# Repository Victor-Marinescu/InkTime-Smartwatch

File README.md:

# InkTime Smartwatch Project

**InkTime** este un smartwatch conceptual bazat pe microcontrolerul **nRF52840**, proiectat pentru autonomie ridicată prin utilizarea unui ecran E-Paper și optimizarea consumului de energie.

---

## 1. Diagramă Bloc
Sistemul este organizat în jurul MCU-ului nRF52840, care gestionează comunicația cu senzorii via I2C și controlul ecranului via SPI.

## 2. Bill Of Materials (BOM)

| Componentă | Descriere | Datasheet |
| :--- | :--- | :--- |
| **nRF52840** | MCU Bluetooth 5.4, ARM Cortex-M4 | [Link](https://jlcpcb.com/partdetail/NordicSemicon-NRF52840_QFAA_FR7/C3606653) |
| **5034802400** | 1.54" E-Paper Display (SPI) | [Link](https://jlcpcb.com/partdetail/MOLEX-5034802400/C122434) |
| **MAX17048** | Fuel Gauge (Monitorizare Baterie) | [Link](https://jlcpcb.com/partdetail/2777647-MAX17048GT10/C2682616) |
| **DRV2605** | Haptic Driver (LRA/ERM) | [Link](https://jlcpcb.com/partdetail/TexasInstruments-DRV2605YZFR/C81079) |
| **LSM6DS3** | IMU (Accelerometru & Giroscop) | [Link](https://jlcpcb.com/partdetail/STMicroelectronics-LSM6DS3TR/C95230) |
| **BQ25180** | IC Management Încărcare Baterie | [Link](https://jlcpcb.com/partdetail/TexasInstruments-BQ25180YBGR/C3682423) |
| **RT6160** | Regulator Buck-Boost 3.3V 2.4A | [Link](https://jlcpcb.com/partdetail/RichtekTech-RT6160AWSC/C7065276) |

---

## 3. Descriere Funcționalitate Hardware

### Module și Senzori
* **Microcontroler (MCU):** nRF52840 (AQFN-73) coordonează procesele BLE și perifericele. Decuplare locală via C14 (4.7 µF), C7/C8/C12 (100 nF).
* **Afișaj E-Paper:** Conectat prin **SPI**. Include pompă de tensiune cu L5 (68 µH) și switch de alimentare Q1/Q3 pentru consum zero în sleep.
* **Haptic Feedback:** Driver DRV2605 (I2C: 0x5A) capabil să ruleze peste 123 de efecte tactile din librăria ROM.
* **Power Management:** * **BQ25180:** Încărcător inteligent (I2C: 0x6A) cu Power Path.
    * **MAX17048:** Monitorizare SOC (I2C: 0x36) via algoritm ModelGauge.
    * **RT6160:** Buck-Boost pentru prag stabil de 3.3V chiar și la descărcarea bateriei sub 3.3V.

---

## 4. Configurație Detaliată Pini (nRF52840)

Am extras configurația completă a pinilor conform mapării hardware finale:

| Pin MCU | AQFN-73 | Funcție | Destinație Hardware | Note Tehnice |
| :--- | :--- | :--- | :--- | :--- |
| **P0.02** | A12 | **SCK** | J1 pin 14 (EPD) | Clock SPI Afișaj |
| **P0.03** | B13 | **MOSI** | J1 pin 15 (EPD) | Date SPI Afișaj |
| **P0.05** | A14 | **CS** | J1 pin 13 (EPD) | Chip Select (Activ LOW) |
| **P0.06** | B15 | **SDA** | I2C Bus Shared | Date senzori (R18 pull-up 3.3k) |
| **P0.07** | A16 | **SCL** | I2C Bus Shared | Clock senzori (R17 pull-up 3.3k) |
| **P0.15** | B19 | **EPD_DC** | J1 pin 11 (EPD) | Data/Command Select |
| **P0.16** | A20 | **EPD_RST**| J1 pin 10 (EPD) | Reset Hardware Afișaj |
| **P0.17** | B21 | **BUSY** | J1 pin 9 (EPD) | Monitorizare stare afișaj |
| **P1.01** | AD22 | **EPD_EN** | Q1 PMOS Gate | Control Power-Cut ecran |
| **P0.13** | AD16 | **SW_UP** | Buton UP | Intrare Digitală (R14 pull-up 10k) |
| **P0.12** | AC17 | **SW_ENT**| Buton ENTER | Intrare Digitală (R15 pull-up 10k) |
| **P0.11** | AD18 | **SW_DN** | Buton DOWN | Intrare Digitală (R16 pull-up 10k) |
| **ANT** | H23 | **RF** | Antenă Ceratent | Adaptare 50 Ω (L1, C3, C4) |
| **SWDIO** | AC24 | **DIO** | J2 pin 2 (Debug) | Programare Serial Wire Data |
| **SWDCLK**| AA24 | **CLK** | J2 pin 4 (Debug) | Programare Serial Wire Clock |

---

## 5. Strategie Design și Review

### Detalii PCB (4 Layere)
* **Lățime Trasee Putere:** 0.3 mm pentru rețelele `VBUS`, `VBAT`, `VREG` și `3V3`.
* **Trasee Date:** 0.15 mm pentru I2C, SPI și semnalele de control.
* **Stackup:**
    * **Layer 1 (Top):** Componente, RF (Antenă) și semnale critice.
    * **Layer 2:** Plan dedicat de alimentare (3.3V / VREG).
    * **Layer 63 (Mid):** Trasee secundare de date.
    * **Layer 64 (Bottom):** Plan de masă (GND) continuu sub zona RF.

### Estimare Consum Energetic
* **MCU (Sleep + RTC + BLE Adv 1Hz):** ~200 µA
* **BMA423 (Pedometru Low-Power):** ~130 µA
* **MAX17048 (Activ):** ~23 µA
* **RT6160 Quiescent:** ~30 µA
* **Total Mediu:** **~390 µA**
* **Autonomie:** ~10 zile (baterie 100mAh) / ~25 zile (baterie 250mAh).

---

## 6. Erori DRC Ignorate 

### Overlap (6 erori)
* **Localizare:** Cele 3 butoane laterale (UP, ENT, DN).
* **Justificare:** Suprapunere asumată între pinii mecanici și via-urile de semnal.

### Drill size (11 erori)
* **Localizare:** Pinii înconjurați de alți pini, fara acces la exterior.
* **Justificare:** S-a folosit câte un via pentru a face conexiunea între pini fără a avea erori de tip Copper Clearance.

### Board Outline Clearance (4 erori)
* **Localizare:** Conector USB-C (J4).
* **Justificare:** Cupru extins până în Dimension layer pentru a asigura fixarea structurală a mufei la marginea carcasei.

---
Licensed under the [Apache 2.0](LICENSE).

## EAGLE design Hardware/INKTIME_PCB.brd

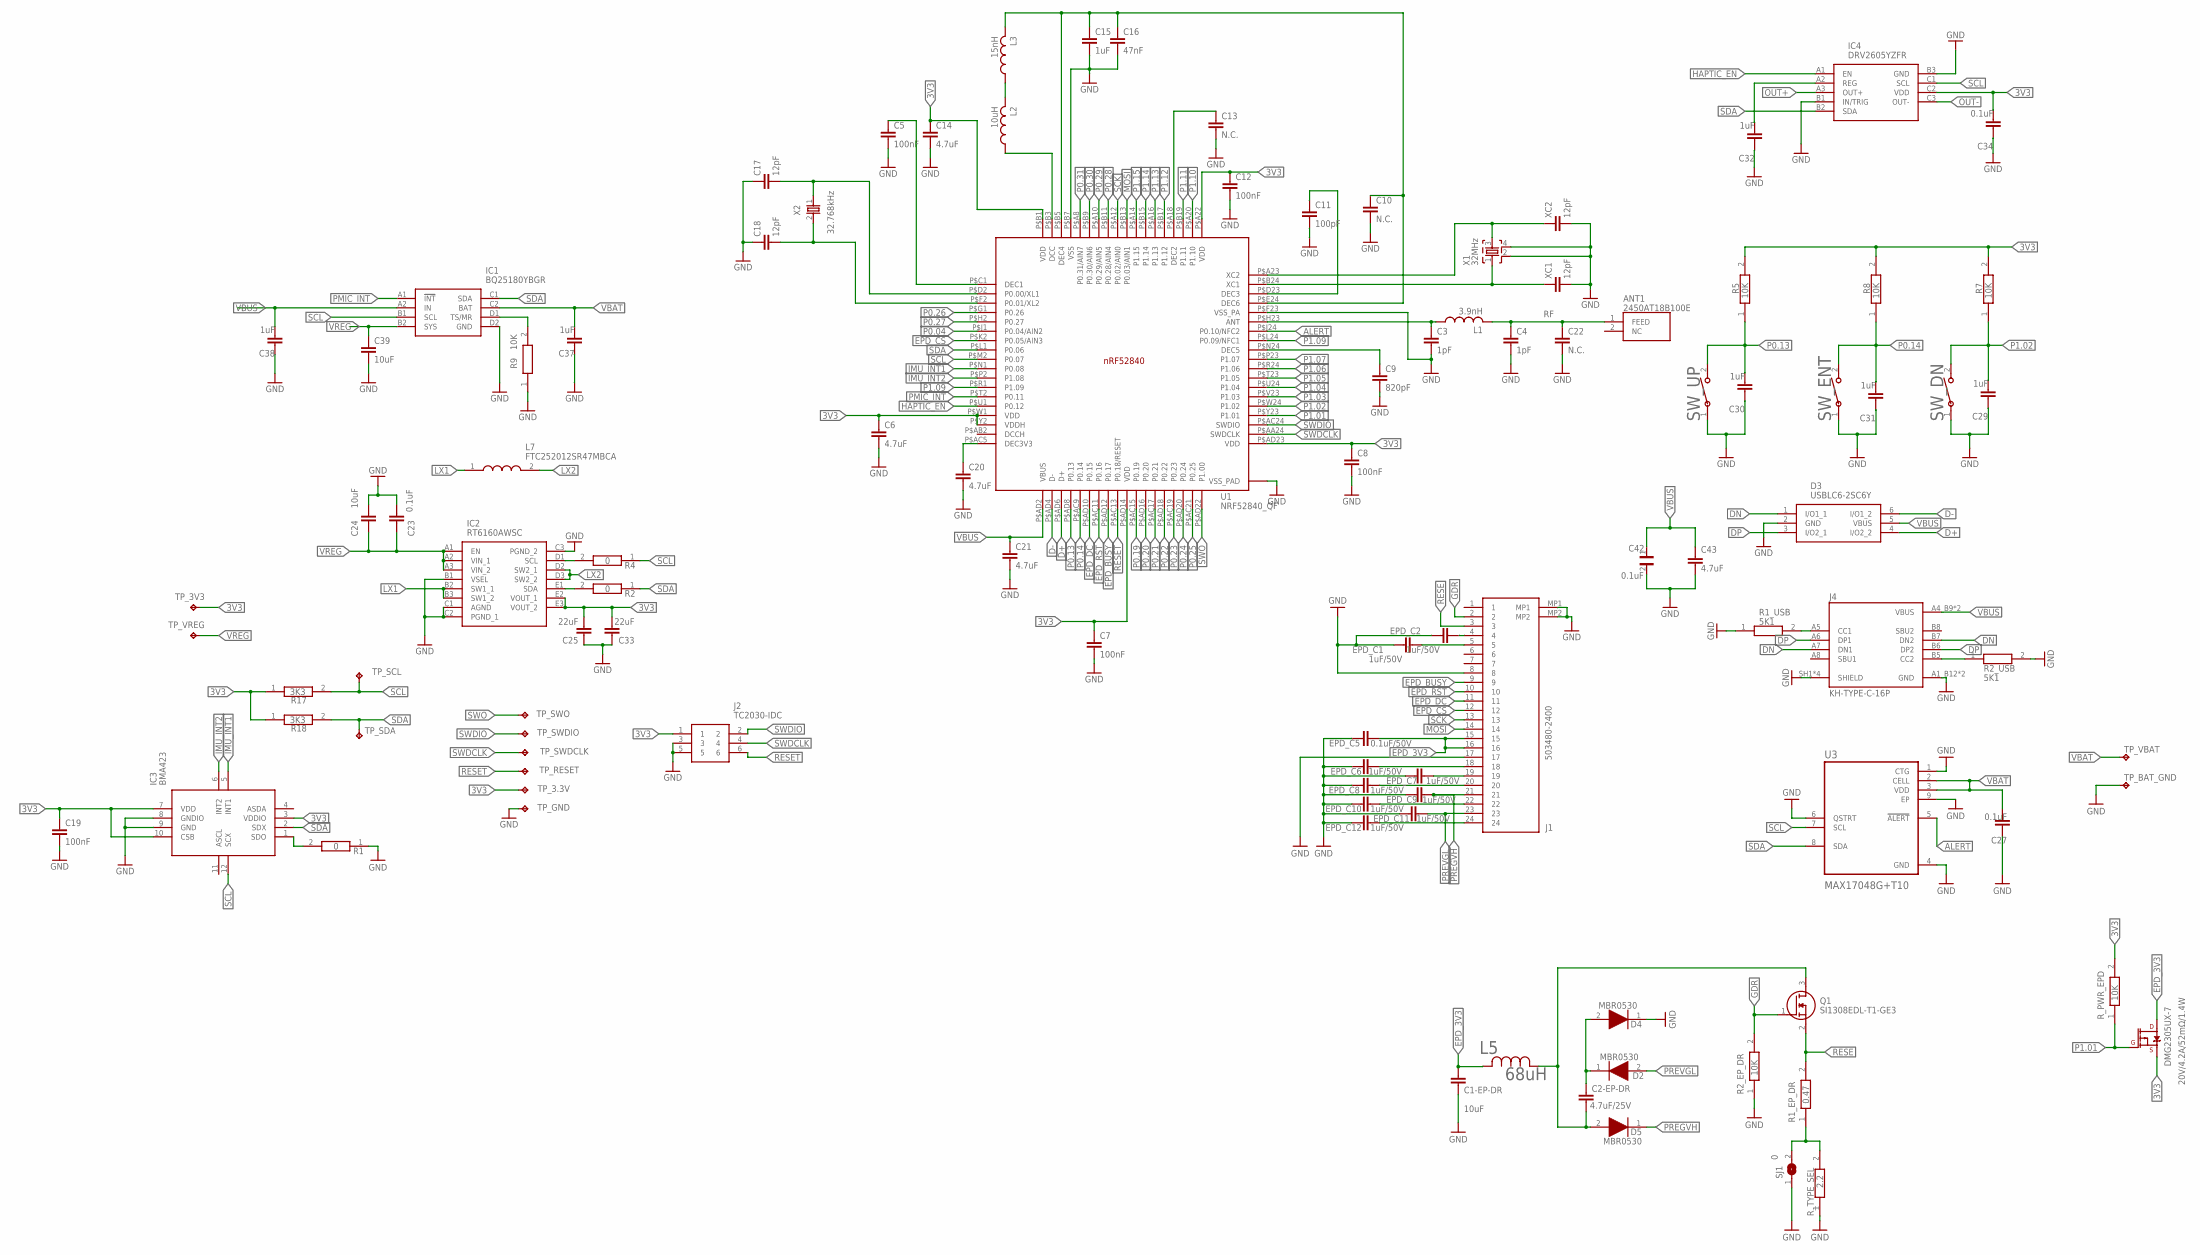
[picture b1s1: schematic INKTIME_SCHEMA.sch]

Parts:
ANT1: 2450AT18B100E; 2450AT18B100E_ANTC3216X140N
C1-EP-DR: 10uF; NORDIC_NRF_3_RESC0402_L
C2-EP-DR: 4.7uF/25V; NORDIC_NRF_3_RESC0402_L
C3, C4: 1pF; NORDIC_NRF_3_RESC0201_L
C5, C7, C8, C12, C19: 100nF; NORDIC_NRF_3_RESC0201_L
C6, C14, C20, C21: 4.7uF; PERFECT_0402_0402
C9: 820pF; NORDIC_NRF_3_RESC0201_L
C10, C13, C22: N.C.; NORDIC_NRF_3_RESC0201_L
C11: 100pF; NORDIC_NRF_3_RESC0201_L
C15, C29, C30, C31, C32: 1uF; NORDIC_NRF_3_RESC0402_L
C16: 47nF; PERFECT_0402_0402
C17, C18: 12pF; NORDIC_NRF_3_RESC0201_L
C23, C27, C34: 0.1uF; NORDIC_NRF_3_RESC0201_L
C24: 10uF; NORDIC_NRF_3_RESC0402_N
C25, C33: 22uF; NORDIC_NRF_3_RESC0402_N
C37, C38: 1uF; NORDIC_NRF_3_RESC0402_N
C39: 10uF; PERFECT_0402_0402
C42: 0.1uF; GRM011R60J152KE01L_1_0201
C43: 4.7uF; NORDIC_NRF_3_RESC0603_N
D2, D4, D5: MBR0530; ESP32_C6_LIBRARY_5_SOD3716X135N
D3: USBLC6-2SC6Y; ESP32_C6_LIBRARY_3_SOT95P280X145-6N
DMG2305UX-7: 20V/4.2A/52mΩ/1.4W; ESP32_C6_LIBRARY_4_ESP32_C6_LIBRARY_4_ESP32_C6_LIBRARY_4_ES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
EPD_C1, EPD_C2, EPD_C6, EPD_C7, EPD_C8, EPD_C9, EPD_C10, EPD_C11, EPD_C12: 1uF/50V; NORDIC_NRF_3_RESC0402_L
EPD_C5: 0.1uF/50V; NORDIC_NRF_3_RESC0201_L
IC1: BQ25180YBGR; BQ25180YBGR_BGA8C40P2X4_100X155X50
IC2: RT6160AWSC; RT6160AWSC_BGA15C40P3X5_140X230X60
IC3: BMA423; BMA423_BMA423
IC4: DRV2605YZFR; DRV2605YZFR_BGA9C50P3X3_144X144X62
J1: 503480-2400; 503480-2400_5034802400
J2: TC2030-IDC; TC2030-IDC_TC2030IDC
J4: KH-TYPE-C-16P; KH-TYPE-C-16P_KINGHELM_KH-TYPE-C-16P
L1: 3.9nH; NORDIC_NRF_2_RESC0201_L
L2: 10uH; NORDIC_NRF_2_RESC0201_L
L3: 15nH; NORDIC_NRF_2_RESC0201_L
L5: 68uH; ESP32_C6_LIBRARY_2_IND_4828-WE-TPC_WRE
L7: FTC252012SR47MBCA; MLP2016SR47MT0S1_INDC2016X100N
Q1: SI1308EDL-T1-GE3; ESP32_C6_LIBRARY_6_SOT65P210X110-3N
R1, R2, R4: 0; CPF0201D7K68C1_0201
R1_EP_DR: 0.47; CPF0201D7K68C1_0201
R1_USB, R2_USB: 5K1; CPF0201D7K68C1_0201
R2_EP_DR, R5, R7, R8, R9: 10K; CPF0201D7K68C1_0201
R17, R18: 3K3; CPF0201D7K68C1_0201
R_PWR_EPD: 10K; CPF0201D7K68C1_0201
R_TYPE_SEL: 2.2; CPF0201D7K68C1_0201
SJ1: 0; ESP32_C6_LIBRARY_7_JUMPER_SJ
SW_DN: 2025-10-22_07-23-44_LIBRARY_EVP-AKE31ASW_EVP-AKE3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; 2025-10-22_07-23-44_LIBRARY_SW_EVP-AKE31A_PAN
SW_ENT: 2025-10-22_07-23-44_LIBRARY_EVP-AKE31ASW_EVP-AKE3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; 2025-10-22_07-23-44_LIBRARY_SW_EVP-AKE31A_PAN
SW_UP: 2025-10-22_07-23-44_LIBRARY_EVP-AKE31ASW_EVP-AKE3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; 2025-10-22_07-23-44_LIBRARY_SW_EVP-AKE31A_PAN
TP_3.3V, TP_3V3: HECTOR_WATCH_1_TPTP20R; HECTOR_WATCH_1_TP20R
TP_BAT_GND: HECTOR_WATCH_1_TPTP20R; HECTOR_WATCH_1_TP20R
TP_GND: HECTOR_WATCH_1_TPTP20R; HECTOR_WATCH_1_TP20R
TP_RESET: HECTOR_WATCH_1_TPTP20R; HECTOR_WATCH_1_TP20R
TP_SCL: HECTOR_WATCH_1_TPTP20R; HECTOR_WATCH_1_TP20R
TP_SDA: HECTOR_WATCH_1_TPTP20R; HECTOR_WATCH_1_TP20R
TP_SWDCLK: HECTOR_WATCH_1_TPTP20R; HECTOR_WATCH_1_TP20R
TP_SWDIO: HECTOR_WATCH_1_TPTP20R; HECTOR_WATCH_1_TP20R
TP_SWO: HECTOR_WATCH_1_TPTP20R; HECTOR_WATCH_1_TP20R
TP_VBAT: HECTOR_WATCH_1_TPTP20R; HECTOR_WATCH_1_TP20R
TP_VREG: HECTOR_WATCH_1_TPTP20R; HECTOR_WATCH_1_TP20R
U1: NRF52840_QF; NORDIC_NRF_4_AQFN50P700X700X85_HS-74N
U3: MAX17048G+T10; ESP32_C6_LIBRARY_SON50P200X200X80-9N
X1: 32MHz; NORDIC_NRF_BT-XTAL_2016_N
X2: 32.768kHz; NORDIC_NRF_1_XTAL_3215_N
XC1, XC2: 12pF; NORDIC_NRF_3_RESC0201_L

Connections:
3V3: C6.1, C7.1, C8.1, C12.1, C14.1, C19.1, C25.1, C33.1, C34.2, DMG2305UX-7.2 (S), IC2.E2 (VOUT_1), IC2.E3 (VOUT_2), IC3.3 (VDDIO), IC3.7 (VDD), IC3.10 (CSB), IC4.C2 (VDD), J2.1, R5.2, R7.2, R8.2, R17.1, R18.1, R_PWR_EPD.2, TP_3.3V.TP, TP_3V3.TP, U1.P$A22 (VDD), U1.P$AD14 (VDD), U1.P$AD23 (VDD), U1.P$B1 (VDD), U1.P$W1 (VDD), U1.P$Y2 (VDDH)
ALERT: U1.P$J24 (P0.10/NFC2), U3.5 (!ALERT)
D+: D3.4 (I/O2_2), U1.P$AD6 (D+)
D-: D3.6 (I/O1_2), U1.P$AD4 (D-)
DN: D3.1 (I/O1_1), J4.A7 (DN1), J4.B7 (DN2)
DP: D3.3 (I/O2_1), J4.A6 (DP1), J4.B6 (DP2)
EPD_3V3: C1-EP-DR.2, DMG2305UX-7.3 (D), EPD_C5.2, J1.15, J1.16, L5.2
EPD_BUSY: J1.9, U1.P$AD12 (P0.17)
EPD_CS: J1.12, U1.P$K2 (P0.05/AIN3)
EPD_DC: J1.11, U1.P$AD10 (P0.15)
EPD_RST: J1.10, U1.P$AC11 (P0.16)
GDR: J1.2, Q1.1 (G), R2_EP_DR.2
GND: C1-EP-DR.1, C3.2, C4.2, C5.2, C6.2, C7.2, C8.2, C9.2, C10.2, C11.2, C12.2, C13.2, C14.2, C15.2, C16.2, C17.1, C18.1, C19.2, C20.2, C21.2, C22.2, C23.1, C24.1, C25.2, C27.1, C29.1, C30.1, C31.1, C32.1, C33.2, C34.1, C37.1, C38.1, C39.2, C42.2, C43.2, D3.2 (GND), D4.1 (K), EPD_C1.1, EPD_C2.1, EPD_C5.1, EPD_C6.1, EPD_C7.1, EPD_C8.1, EPD_C9.1, EPD_C10.1, EPD_C11.1, EPD_C12.1, IC1.D2 (GND), IC2.B1 (VSEL), IC2.C1 (AGND), IC2.C2 (PGND_1), IC2.C3 (PGND_2), IC3.8 (GNDIO), IC3.9 (GND), IC4.B1 (IN/TRIG), IC4.B3 (GND), J1.8, J1.17, J1.MP1, J1.MP2, J2.3, J2.5, J4.A1_B12 (GND), J4.A12_B1 (GND), J4.SH1 (SHIELD), J4.SH2 (SHIELD), J4.SH3 (SHIELD), J4.SH4 (SHIELD), R1.1, R1_USB.1, R2_EP_DR.1, R2_USB.2, R9.1, R_TYPE_SEL.1, SJ1.1, SW_DN.1, SW_ENT.1, SW_UP.1, TP_BAT_GND.TP, TP_GND.TP, U1.P$74 (VSS_PAD), U1.P$75 (VSS_PAD), U1.P$76 (VSS_PAD), U1.P$77 (VSS_PAD), U1.P$78 (VSS_PAD), U1.P$79 (VSS_PAD), U1.P$80 (VSS_PAD), U1.P$81 (VSS_PAD), U1.P$82 (VSS_PAD), U1.P$83 (VSS_PAD), U1.P$84 (VSS_PAD), U1.P$85 (VSS_PAD), U1.P$86 (VSS_PAD), U1.P$87 (VSS_PAD), U1.P$88 (VSS_PAD), U1.P$89 (VSS_PAD), U1.P$90 (VSS_PAD), U1.P$B7 (VSS), U1.P$F23 (VSS_PA), U3.1 (CTG), U3.4 (GND), U3.6 (QSTRT), U3.9 (EP), X1.2, X1.4, XC1.2, XC2.2
HAPTIC_EN: IC4.A1 (EN), U1.P$U1 (P0.12)
IMU_INT1: IC3.5 (INT1), U1.P$N1 (P0.08)
IMU_INT2: IC3.6 (INT2), U1.P$P2 (P1.08)
LX1: IC2.B2 (SW1_1), IC2.B3 (SW1_2), L7.1
LX2: IC2.D2 (SW2_1), IC2.D3 (SW2_2), L7.2
MOSI: J1.14, U1.P$B13 (P0.03/AIN1)
unnamed: IC2.D1 (SCL), R4.2
unnamed: IC1.D1 (TS/MR), R9.2
unnamed: IC2.E1 (SDA), R2.2
unnamed: U1.P$B24 (XC1), X1.1, XC1.1
unnamed: U1.P$A23 (XC2), X1.3, XC2.1
unnamed: C10.1, C15.1, C16.1, L3.2, U1.P$B5 (DEC4), U1.P$E24 (DEC6)
unnamed: IC3.1 (SDO), R1.2
unnamed: L2.2, L3.1
unnamed: C13.1, U1.P$A18 (DEC2)
unnamed: L2.1, U1.P$B3 (DCC)
unnamed: C32.2, IC4.A2 (REG)
unnamed: C5.1, U1.P$C1 (DEC1)
unnamed: EPD_C6.2, J1.18
unnamed: C9.1, U1.P$N24 (DEC5)
unnamed: C17.2, U1.P$D2 (P0.00/XL1), X2.1
unnamed: C18.2, U1.P$F2 (P0.01/XL2), X2.2
unnamed: C20.1, U1.P$AC5 (DEC3V3)
unnamed: C3.1, L1.1, U1.P$H23 (ANT)
unnamed: EPD_C12.2, J1.24
unnamed: EPD_C2.2, J1.4
unnamed: C11.1, U1.P$D23 (DEC3)
unnamed: J4.B5 (CC2), R2_USB.1
unnamed: J4.A5 (CC1), R1_USB.2
unnamed: EPD_C1.2, J1.5
unnamed: EPD_C10.2, J1.22
unnamed: EPD_C8.2, J1.20
unnamed: EPD_C7.2, J1.19
unnamed: R1_EP_DR.1, R_TYPE_SEL.2, SJ1.2
unnamed: C2-EP-DR.1, D5.2 (A), L5.1, Q1.3 (D)
unnamed: C2-EP-DR.2, D2.1 (K), D4.2 (A)
OUT+: IC4.A3 (OUT+)
OUT-: IC4.C3 (OUT-)
P0.04: U1.P$J1 (P0.04/AIN2)
P0.13: C30.2, R5.1, SW_UP.2, U1.P$AD8 (P0.13)
P0.14: C31.2, R8.1, SW_ENT.2, U1.P$AC9 (P0.14)
P0.19: U1.P$AC15 (P0.19)
P0.20: U1.P$AD16 (P0.20)
P0.21: U1.P$AC17 (P0.21)
P0.22: U1.P$AD18 (P0.22)
P0.23: U1.P$AC19 (P0.23)
P0.24: U1.P$AD20 (P0.24)
P0.25: U1.P$AC21 (P0.25)
P0.26: U1.P$G1 (P0.26)
P0.27: U1.P$H2 (P0.27)
P0.28: U1.P$B11 (P0.28/AIN4)
P0.29: U1.P$A10 (P0.29/AIN5)
P0.30: U1.P$B9 (P0.30/AIN6)
P0.31: U1.P$A8 (P0.31/AIN7)
P1.01: DMG2305UX-7.1 (G), R_PWR_EPD.1, U1.P$Y23 (P1.01)
P1.02: C29.2, R7.1, SW_DN.2, U1.P$W24 (P1.02)
P1.03: U1.P$V23 (P1.03)
P1.04: U1.P$U24 (P1.04)
P1.05: U1.P$T23 (P1.05)
P1.06: U1.P$R24 (P1.06)
P1.07: U1.P$P23 (P1.07)
P1.09: U1.P$L24 (P0.09/NFC1), U1.P$R1 (P1.09)
P1.10: U1.P$A20 (P1.10)
P1.11: U1.P$B19 (P1.11)
P1.12: U1.P$B17 (P1.12)
P1.13: U1.P$A16 (P1.13)
P1.14: U1.P$B15 (P1.14)
P1.15: U1.P$A14 (P1.15)
PMIC_INT: IC1.A1 (!INT), U1.P$T2 (P0.11)
PREGVH: D5.1 (K), EPD_C9.2, J1.21
PREVGL: D2.2 (A), EPD_C11.2, J1.23
RESE: J1.3, Q1.2 (S), R1_EP_DR.2
RESET: J2.6, TP_RESET.TP, U1.P$AC13 (P0.18/RESET)
RF: ANT1.1 (FEED), C4.1, C22.1, L1.2
SCK: J1.13, U1.P$A12 (P0.02/AIN0)
SCL: IC1.B1 (SCL), IC3.12 (SCX), IC4.C1 (SCL), R4.1, R17.2, TP_SCL.TP, U1.P$M2 (P0.07), U3.7 (SCL)
SDA: IC1.C1 (SDA), IC3.2 (SDX), IC4.B2 (SDA), R2.1, R18.2, TP_SDA.TP, U1.P$L1 (P0.06), U3.8 (SDA)
SWDCLK: J2.4, TP_SWDCLK.TP, U1.P$AA24 (SWDCLK)
SWDIO: J2.2, TP_SWDIO.TP, U1.P$AC24 (SWDIO)
SWO: TP_SWO.TP, U1.P$AD22 (P1.00)
VBAT: C27.2, C37.2, IC1.C2 (BAT), TP_VBAT.TP, U3.2 (CELL), U3.3 (VDD)
VBUS: C21.1, C38.2, C42.1, C43.1, D3.5 (VBUS), IC1.A2 (IN), J4.A4_B9 (VBUS), J4.A9_B4 (VBUS), U1.P$AD2 (VBUS)
VREG: C23.2, C24.2, C39.1, IC1.B2 (SYS), IC2.A1 (EN), IC2.A2 (VIN_1), IC2.A3 (VIN_2), TP_VREG.TP

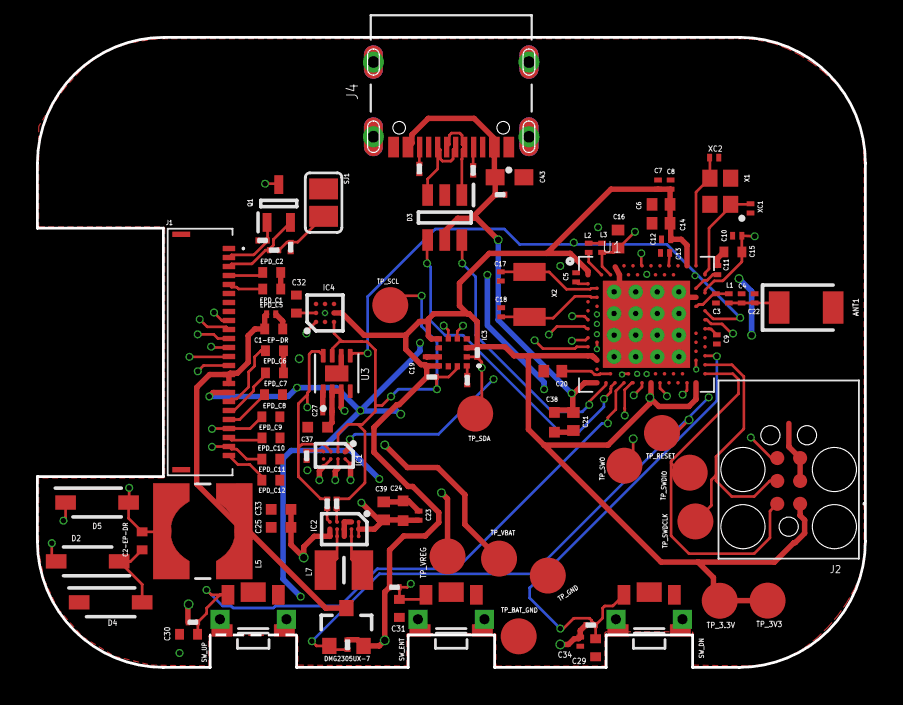
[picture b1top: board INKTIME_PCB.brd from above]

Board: 4 copper layers, 46.0 x 35.0 mm, 103 parts (0 on the bottom side), 69 nets.

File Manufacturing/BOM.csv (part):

Qty,Value,Device,Package,Parts,Description,ARROW_PART_NUMBER,ARROW_PRICE-STOCK,AVAILABILITY,CHECK_PRICES,COPYRIGHT,DESCRIPTION,DIGI-KEY_PART_NUMBER_1,DIGI-KEY_PART_NUMBER_2,DIGI-KEY_PART_NUMBER_3,HEIGHT,JLCPCB,MANUFACTURER_NAME,MANUFACTURER_PART_NUMBER,MF,MFR_NAME,MOUSER_PART_NUMBER,MOUSER_PRICE-STOCK,MP,PACKAGE,POPULARITY,PRICE,PROD_ID,PURCHASE-URL,SNAPEDA_LINK,TP_SIGNAL_NAME,VALUE
3,0,CPF0201D7K68C1_CPF0201D7K68C1,CPF0201D7K68C1_0201,"R1, R2, R4","7.68k 0201 Thin Film Surface Mount Fixed Resistor +/-0.5% 0.031W CPF0201D7K68C1",,,,,,,,,,,,,,,,,,,,,,,,,,
1,0,ESP32_C6_LIBRARY_7_JUMPER_SJ,ESP32_C6_LIBRARY_7_JUMPER_SJ,SJ1,"SMD solder JUMPER",,,,,,,,,,,,,,,,,,,,3,,,,,,
1,0.1uF,GRM011R60J152KE01L_1_GRM011R60J152KE01L,GRM011R60J152KE01L_1_0201,C42,"Check availability",,,,,,,,,,,,,,,,,,,,,,,,,,
3,0.1uF,NORDIC_NRF_3_CAPACITOR_0201_L,NORDIC_NRF_3_RESC0201_L,"C23, C27, C34","Generic chip capacitor",,,,,,,,,,,,,,,,,,,,,,,,,,
1,0.1uF/50V,NORDIC_NRF_3_CAPACITOR_0201_L,NORDIC_NRF_3_RESC0201_L,EPD_C5,"Generic chip capacitor",,,,,,,,,,,,,,,,,,,,,,,,,,
1,0.47,CPF0201D7K68C1_CPF0201D7K68C1,CPF0201D7K68C1_0201,R1_EP_DR,"7.68k 0201 Thin Film Surface Mount Fixed Resistor +/-0.5% 0.031W CPF0201D7K68C1",,,,,,,,,,,,,,,,,,,,,,,,,,
5,100nF,NORDIC_NRF_3_CAPACITOR_0201_L,NORDIC_NRF_3_RESC0201_L,"C5, C7, C8, C12, C19","Generic chip capacitor",,,,,,,,,,,,,,,,,,,,,,,,,,
1,100pF,NORDIC_NRF_3_CAPACITOR_0201_L,NORDIC_NRF_3_RESC0201_L,C11,"Generic chip capacitor",,,,,,,,,,,,,,,,,,,,,,,,,,
6,10K,CPF0201D7K68C1_CPF0201D7K68C1,CPF0201D7K68C1_0201,"R2_EP_DR, R5, R7, R8, R9, R_PWR_EPD","7.68k 0201 Thin Film Surface Mount Fixed Resistor +/-0.5% 0.031W CPF0201D7K68C1",,,,,,,,,,,,,,,,,,,,,,,,,,
1,10uF,NORDIC_NRF_3_CAPACITOR_0402_L,NORDIC_NRF_3_RESC0402_L,C1-EP-DR,"Generic chip capacitor",,,,,,,,,,,,,,,,,,,,,,,,,,
1,10uF,NORDIC_NRF_3_CAPACITOR_0402_N,NORDIC_NRF_3_RESC0402_N,C24,"Generic chip capacitor",,,,,,,,,,,,,,,,,,,,,,,,,,
1,10uF,PERFECT_0402_CAP_0402,PERFECT_0402_0402,C39,"0402 (1005 Metric)",,,,,,,,,,,,,,,,,,,,,,,,,,
1,10uH,NORDIC_NRF_2_INDUCTOR_0201_L,NORDIC_NRF_2_RESC0201_L,L2,"Generic chip inductor",,,,,,,,,,,,,,,,,,,,,,,,,,
4,12pF,NORDIC_NRF_3_CAPACITOR_0201_L,NORDIC_NRF_3_RESC0201_L,"C17, C18, XC1, XC2","Generic chip capacitor",,,,,,,,,,,,,,,,,,,,,,,,,,
1,15nH,NORDIC_NRF_2_INDUCTOR_0201_L,NORDIC_NRF_2_RESC0201_L,L3,"Generic chip inductor",,,,,,,,,,,,,,,,,,,,,,,,,,
2,1pF,NORDIC_NRF_3_CAPACITOR_0201_L,NORDIC_NRF_3_RESC0201_L,"C3, C4","Generic chip capacitor",,,,,,,,,,,,,,,,,,,,,,,,,,
5,1uF,NORDIC_NRF_3_CAPACITOR_0402_L,NORDIC_NRF_3_RESC0402_L,"C15, C29, C30, C31, C32","Generic chip capacitor",,,,,,,,,,,,,,,,,,,,,,,,,,
2,1uF,NORDIC_NRF_3_CAPACITOR_0402_N,NORDIC_NRF_3_RESC0402_N,"C37, C38","Generic chip capacitor",,,,,,,,,,,,,,,,,,,,,,,,,,
9,1uF/50V,NORDIC_NRF_3_CAPACITOR_0402_L,NORDIC_NRF_3_RESC0402_L,"EPD_C1, EPD_C2, EPD_C6, EPD_C7, EPD_C8, EPD_C9, EPD_C10, EPD_C11, EPD_C12","Generic chip capacitor",,,,,,,,,,,,,,,,,,,,,,,,,,
1,2.2,CPF0201D7K68C1_CPF0201D7K68C1,CPF0201D7K68C1_0201,R_TYPE_SEL,"7.68k 0201 Thin Film Surface Mount Fixed Resistor +/-0.5% 0.031W CPF0201D7K68C1",,,,,,,,,,,,,,,,,,,,,,,,,,
3,2025-10-22_07-23-44_LIBRARY_EVP-AKE31ASW_EVP-AKE31A_PAN,2025-10-22_07-23-44_LIBRARY_EVP-AKE31ASW_EVP-AKE31A_PAN,2025-10-22_07-23-44_LIBRARY_SW_EVP-AKE31A_PAN,"SW_DN, SW_ENT, SW_UP",,,,,,"Copyright (C) 2025 Ultra Librarian. All rights reserved.",,P123437TR-ND,P123437CT-ND,P123437DKR-ND,,,Panasonic,EVP-AKE31A,,,,,,,,,,,,,
1,20V/4.2A/52mO/1.4W,ESP32_C6_LIBRARY_4_ESP32_WROVER_SPARKFUN-DISCRETESEMI_MOSFET_PCH-DMG2305UX-7,ESP32_C6_LIBRARY_4_ESP32_C6_LIBRARY_4_ESP32_C6_LIBRARY_4_ESP32_C6_LIBRARY_4_ESP32_WROVER_SPARKFUN-DISCRETESEMI_SOT23-3,DMG2305UX-7,"P-channel MOSFETs",,,,,,,,,,,,,,,,,,,,,,TRAN-14388,,,,20V/4.2A/52mO/1.4W
2,22uF,NORDIC_NRF_3_CAPACITOR_0402_N,NORDIC_NRF_3_RESC0402_N,"C25, C33","Generic chip capacitor",,,,,,,,,,,,,,,,,,,,,,,,,,
1,2450AT18B100E,2450AT18B100E_2450AT18B100E,2450AT18B100E_ANTC3216X140N,ANT1,"Antennas 2.45GHz ANTENNA",2450AT18B100E,https://www.arrow.com/en/products/2450at18b100e/johanson-die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,,,,"Antennas 2.45GHz ANTENNA",,,,1.4mm,,"JOHANSON TECHNOLOGY",2450AT18B100E,,,609-2450AT18B100E,https://www.mouser.co.uk/ProductDetail/Johanson-Technology/2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,,,,,,,,,
1,3.9nH,NORDIC_NRF_2_INDUCTOR_0201_L,NORDIC_NRF_2_RESC0201_L,L1,"Generic chip inductor",,,,,,,,,,,,,,,,,,,,,,,,,,
1,32.768kHz,NORDIC_NRF_1_XTAL_32KHZ,NORDIC_NRF_1_XTAL_3215_N,X2,,,,,,,,,,,,,,,,,,,,,,,,,,,
1,32MHz,NORDIC_NRF_XTAL_32MHZ,NORDIC_NRF_BT-XTAL_2016_N,X1,,,,,,,,,,,,,,,,,,,,,,,,,,,
2,3K3,CPF0201D7K68C1_CPF0201D7K68C1,CPF0201D7K68C1_0201,"R17, R18","7.68k 0201 Thin Film Surface Mount Fixed Resistor +/-0.5% 0.031W CPF0201D7K68C1",,,,,,,,,,,,,,,,,,,,,,,,,,
1,4.7uF,NORDIC_NRF_3_CAPACITOR_0603_N,NORDIC_NRF_3_RESC0603_N,C43,"Generic chip capacitor",,,,,,,,,,,,,,,,,,,,,,,,,,
4,4.7uF,PERFECT_0402_CAP_0402,PERFECT_0402_0402,"C6, C14, C20, C21","0402 (1005 Metric)",,,,,,,,,,,,,,,,,,,,,,,,,,
1,4.7uF/25V,NORDIC_NRF_3_CAPACITOR_0402_L,NORDIC_NRF_3_RESC0402_L,C2-EP-DR,"Generic chip capacitor",,,,,,,,,,,,,,,,,,,,,,,,,,
1,47nF,PERFECT_0402_CAP_0402,PERFECT_0402_0402,C16,"0402 (1005 Metric)",,,,,,,,,,,,,,,,,,,,,,,,,,
1,503480-2400,503480-2400_503480-2400,503480-2400_5034802400,J1,"FFC & FPC Connectors 0.5mm FPC RA SMT Dual Contact 24Ckt",,,,,,"FFC & FPC Connectors 0.5mm FPC RA SMT Dual Contact 24Ckt",,,,1.87mm,,Molex,503480-2400,,,538-503480-2400,https://www.mouser.co.uk/ProductDetail/Molex/503480-2400?qs=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,,,,,,,,,
2,5K1,CPF0201D7K68C1_CPF0201D7K68C1,CPF0201D7K68C1_0201,"R1_USB, R2_USB","7.68k 0201 Thin Film Surface Mount Fixed Resistor +/-0.5% 0.031W CPF0201D7K68C1",,,,,,,,,,,,,,,,,,,,,,,,,,
1,68uH,ESP32_C6_LIBRARY_2_744043680IND_4828-WE-TPC_WRE,ESP32_C6_LIBRARY_2_IND_4828-WE-TPC_WRE,L5,,,,,,"Copyright (C) 2024 Ultra Librarian. All rights reserved.",,,,,,,,744043680,,"Wurth Electronics",,,,,,,,,,,
1,820pF,NORDIC_NRF_3_CAPACITOR_0201_L,NORDIC_NRF_3_RESC0201_L,C9,"Generic chip capacitor",,,,,,,,,,,,,,,,,,,,,,,,,,
1,BMA423,BMA423_BMA423,BMA423_BMA423,IC3,"Accelerometers Triaxial low-g 12bit Acceleration Sensor",BMA423,https://www.arrow.com/en/products/bma423/bosch,,,,"Accelerometers Triaxial low-g 12bit Acceleration Sensor",,,,1mm,,BOSCH,BMA423,,,262-BMA423,https://www.mouser.co.uk/ProductDetail/Bosch-Sensortec/BMA42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,,,,,,,,,
1,BQ25180YBGR,BQ25180YBGR_BQ25180YBGR,BQ25180YBGR_BGA8C40P2X4_100X155X50,IC1,"Charger IC Lithium Ion/Polymer, Lithium Iron Phosphate 8-DSBGA (1.6x1.1)",BQ25180YBGR,https://www.arrow.com/en/products/bq25180ybgr/texas-instrume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,,,,"Charger IC Lithium Ion/Polymer"," Lithium Iron Phosphate 8-DSBGA (1.6x1.1)",,,,0.5mm,,"Texas Instruments",BQ25180YBGR,,,595-BQ25180YBGR,https://www.mouser.co.uk/ProductDetail/Texas-Instruments/BQ2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,,,,,,,,
1,DRV2605YZFR,DRV2605YZFR_DRV2605YZFR,DRV2605YZFR_BGA9C50P3X3_144X144X62,IC4,"Haptic Driver for ERM/LRA with Built-In Library and Smart Loop Architecture",DRV2605YZFR,https://www.arrow.com/en/products/drv2605yzfr/texas-instrume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,,,,"Haptic Driver for ERM/LRA with Built-In Library and Smart Loop Architecture",,,,0.625mm,,"Texas Instruments",DRV2605YZFR,,,,,,,,,,,,,
1,FTC252012SR47MBCA,MLP2016SR47MT0S1_FTC252012SR47MBCA,MLP2016SR47MT0S1_INDC2016X100N,L7,"SMD / SMT Inductors (Coils), L=0.47?H, L x W x T :",,,,,,"SMD / SMT Inductors (Coils)"," L=0.47?H"," L x W x T :",,,,1mm,https://jlcpcb.com/partdetail/6763488-FTC252012SR47MBCA/C5832368,TDK,FTC252012SR47MBCA,,,,,,,,,,,
12,HECTOR_WATCH_1_TPTP20R,HECTOR_WATCH_1_TPTP20R,HECTOR_WATCH_1_TP20R,"TP_3.3V, TP_3V3, TP_BAT_GND, TP_GND, TP_RESET, TP_SCL, TP_SDA, TP_SWDCLK, TP_SWDIO, TP_SWO, TP_VBAT, TP_VREG","Test pad",,,,,,,,,,,,,,,,,,,,2,,,,,,
1,KH-TYPE-C-16P,KH-TYPE-C-16P_KH-TYPE-C-16P,KH-TYPE-C-16P_KINGHELM_KH-TYPE-C-16P,J4,"Check availability",,,"Not in stock",https://www.snapeda.com/parts/KH-TYPE-C-16P/Kinghelm/view-pa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,,"                                                                                                    ",,,,,,,,kinghelm,,,,KH-TYPE-C-16P,None,,None,,,https://www.snapeda.com/parts/KH-TYPE-C-16P/Kinghelm/view-pa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,,
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
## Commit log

2026-04-10 Prima versiune: SCH, PCB, 3D si documentatie
2026-04-10 Readme added
2026-04-11 fix issue 1
2026-04-14 Fixed Issue 2
2026-04-20 Fixed all issues, have to replace placeholder in readme
2026-04-20 Added Manufacturing files
2026-04-21 Readme completed
2026-04-21 Readme formating fixed

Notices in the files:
parts and their libraries:
COPYRIGHT: Copyright (C) 2024 Ultra Librarian. All rights reserved.
COPYRIGHT: Copyright (C) 2025 Ultra Librarian. All rights reserved.
